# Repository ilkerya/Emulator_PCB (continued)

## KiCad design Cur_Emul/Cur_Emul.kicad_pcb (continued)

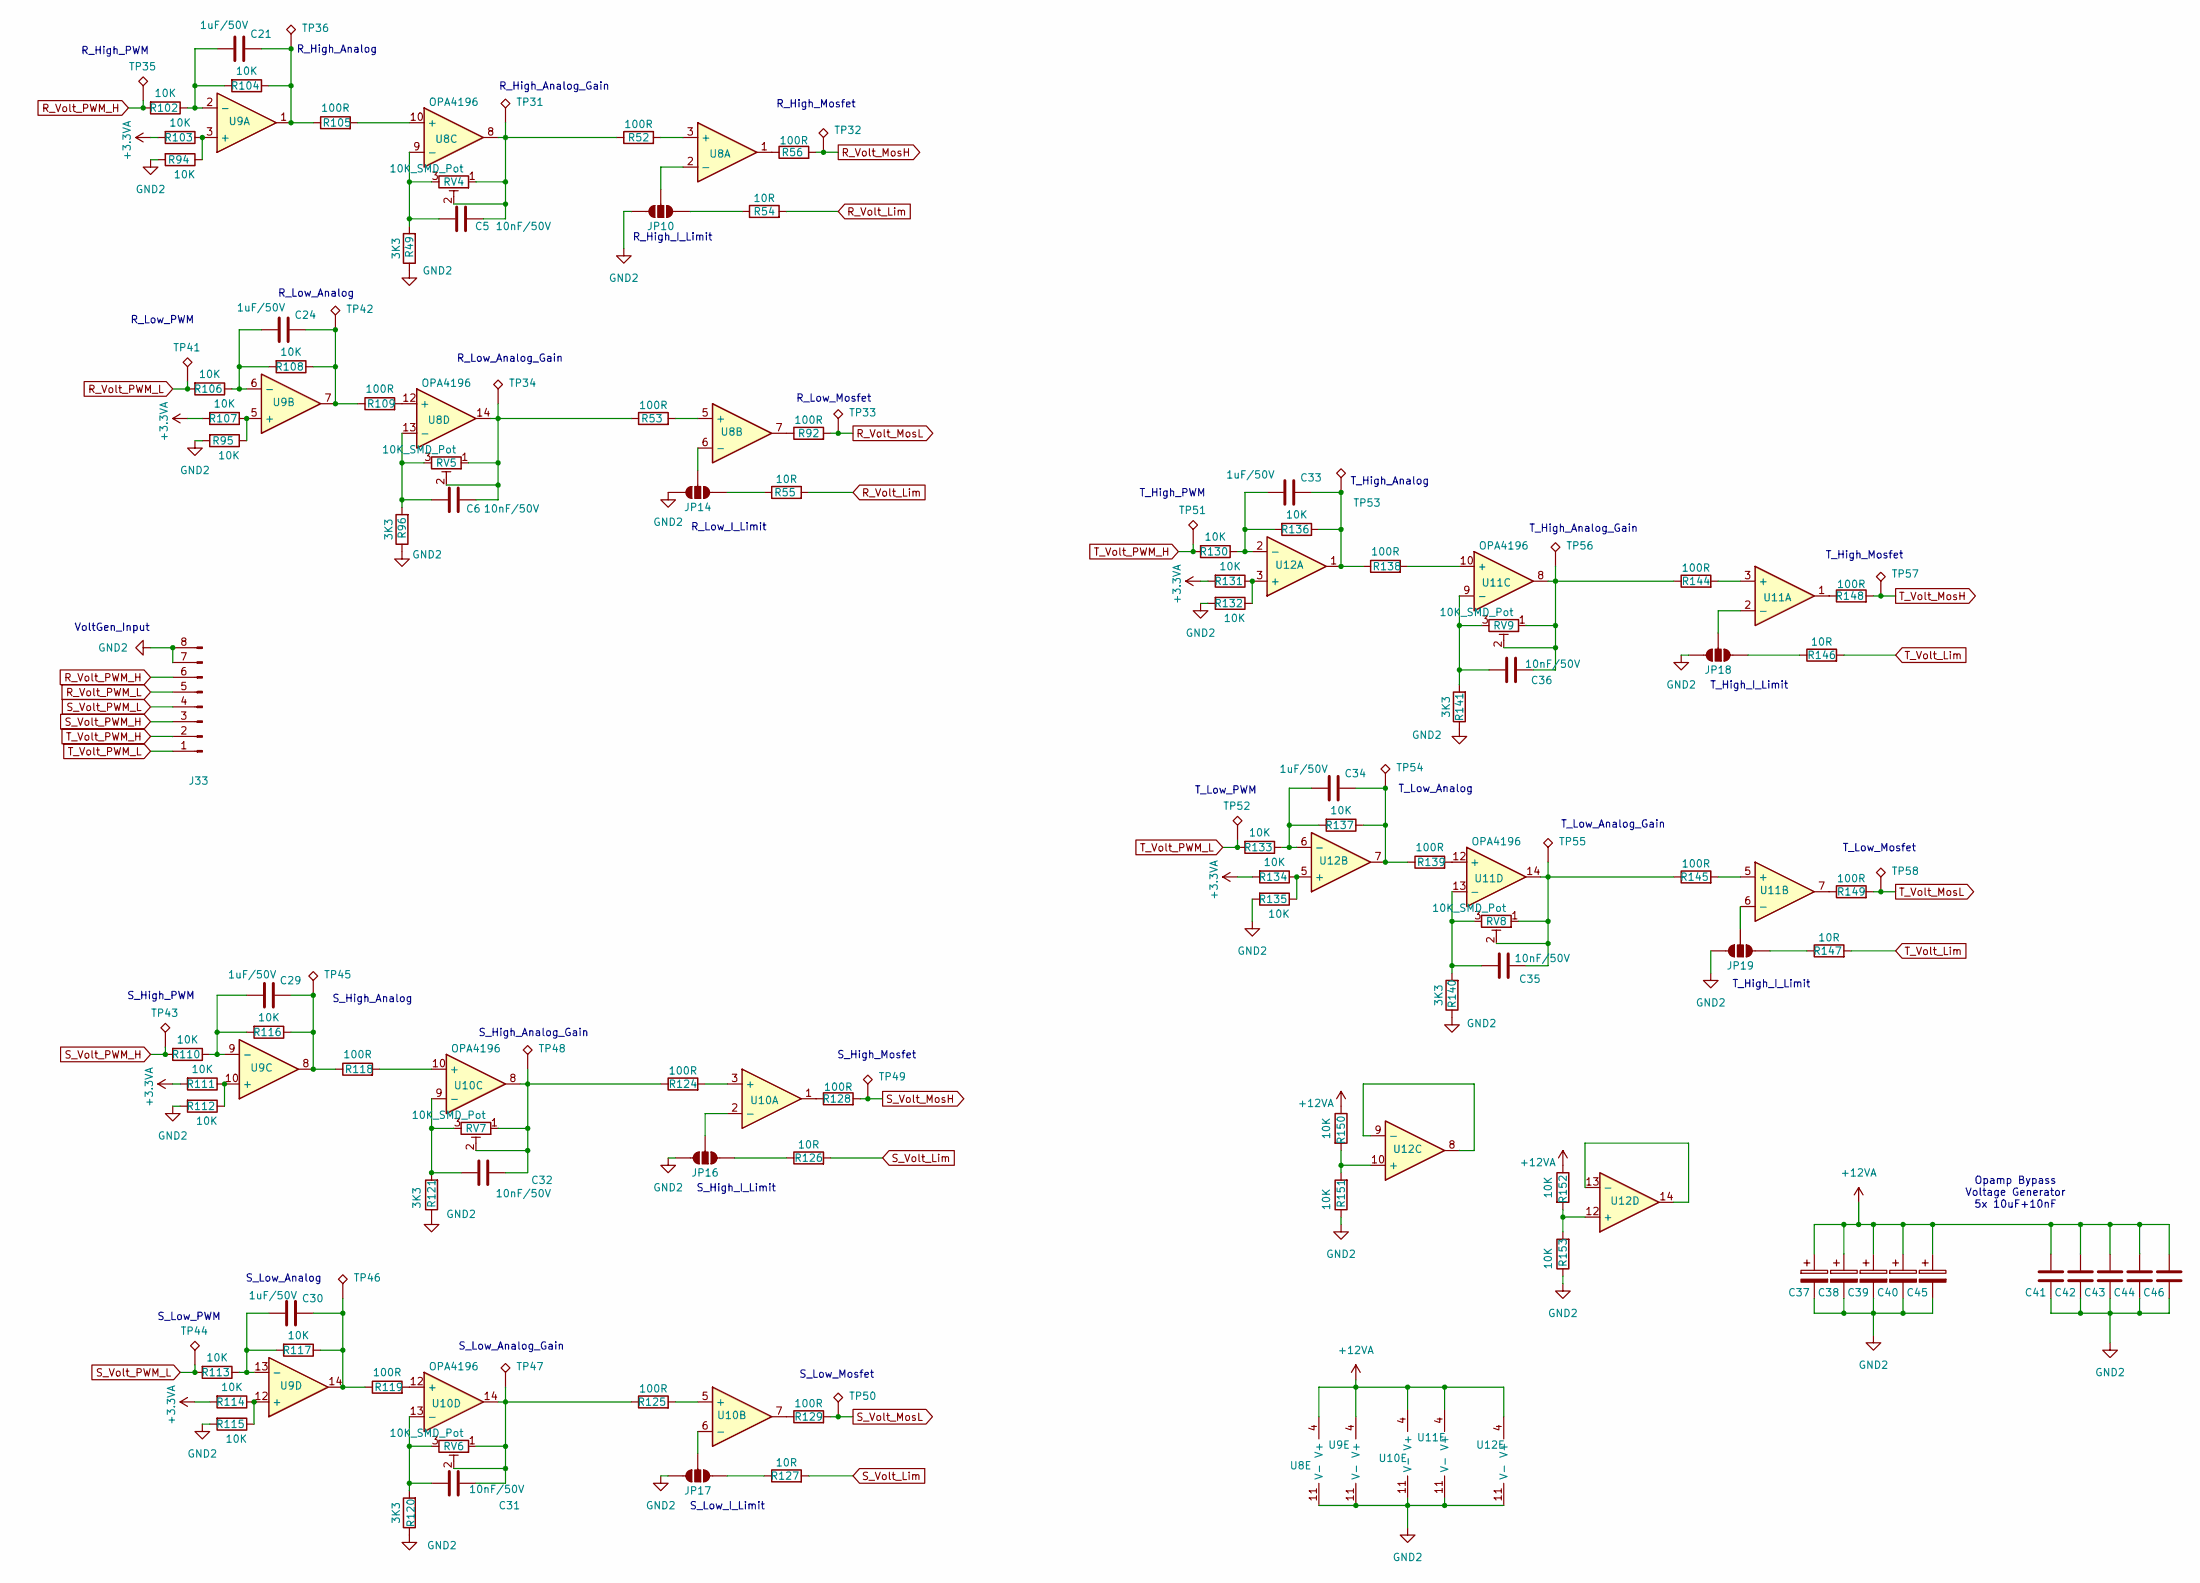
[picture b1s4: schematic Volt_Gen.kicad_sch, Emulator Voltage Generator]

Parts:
C5, C6, C31, C32, C35, C36, C41, C42, C43, C44, C46: 10nF/50V; C_0805_2012Metric_Pad1.18x1.45mm_HandSolder
C21, C24, C29, C30, C33, C34: 1uF/50V; C_1206_3216Metric_Pad1.33x1.80mm_HandSolder
C37, C38, C39, C40, C45: 10uF/50V; CP_Elec_4x3.9
J33: Conn_01x08_Pin_JST_2.0mm; JST_PH_B8B-PH-K_1x08_P2.00mm_Vertical
JP10, JP14, JP16, JP17, JP18, JP19: SolderJumper_3_Open; SolderJumper-3_P2.0mm_Open_TrianglePad1.0x1.5mm
R49, R96, R120, R121, R140, R141: 3K3; R_0805_2012Metric_Pad1.20x1.40mm_HandSolder
R52, R53, R56, R92, R105, R109, R118, R119, R124, R125, R128, R129, R138, R139, R144, R145, R148, R149: 100R; R_0805_2012Metric_Pad1.20x1.40mm_HandSolder
R54, R55, R126, R127, R146, R147: 10R; R_0805_2012Metric_Pad1.20x1.40mm_HandSolder
R94, R95, R102, R103, R104, R106, R107, R108, R110, R111, R112, R113, R114, R115, R116, R117, R130, R131, R132, R133, R134, R135, R136, R137, R150, R151, R152, R153: 10K; R_0805_2012Metric_Pad1.20x1.40mm_HandSolder
RV4, RV5, RV6, RV7, RV8, RV9: 10K_SMD_Pot; Potentiometer_Bourns_3314J_Vertical
TP31, TP32, TP33, TP34, TP35, TP36, TP41, TP42, TP43, TP44, TP45, TP46, TP47, TP48, TP49, TP50, TP51, TP52, TP53, TP54, TP55, TP56, TP57, TP58: Test_Point_THT_KeyStone; TestPoint_Loop_D1.80mm_Drill1.0mm_Beaded
U8, U9, U10, U11, U12: Opamp_Quad_OPA_4196; SOIC-14_3.9x8.7mm_P1.27mm

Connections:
+3.3VA: R103.2, R107.2, R111.2, R114.2, R131.2, R134.2; also elsewhere on the board
+12VA: C37.1, C38.1, C39.1, C40.1, C41.1, C42.1, C43.1, C44.1, C45.1, C46.1, R150.1, R152.1, U8.4 (V+), U9.4 (V+), U10.4 (V+), U11.4 (V+), U12.4 (V+); also elsewhere on the board
GND2: C37.2, C38.2, C39.2, C40.2, C41.2, C42.2, C43.2, C44.2, C45.2, C46.2, J33.7, J33.8, JP10.3 (B), JP14.3 (B), JP16.3 (B), JP17.3 (B), JP18.3 (B), JP19.3 (B), R49.1, R94.2, R95.2, R96.1, R112.2, R115.2, R120.1, R121.1, R132.2, R135.2, R140.1, R141.1, R151.1, R153.1, U8.11 (V-), U9.11 (V-), U10.11 (V-), U11.11 (V-), U12.11 (V-); also elsewhere on the board
unnamed: C5.2, R52.1, RV4.1, RV4.2, TP31.1, U8.8
unnamed: C6.2, R53.1, RV5.1, RV5.2, TP34.1, U8.14
unnamed: C21.2, R104.1, R105.1, TP36.1, U9.1
unnamed: C24.2, R108.1, R109.1, TP42.1, U9.7
unnamed: C29.2, R116.1, R118.1, TP45.1, U9.8
unnamed: C30.2, R117.1, R119.1, TP46.1, U9.14
unnamed: C31.2, R125.1, RV6.1, RV6.2, TP47.1, U10.14
unnamed: C32.2, R124.1, RV7.1, RV7.2, TP48.1, U10.8
unnamed: C33.2, R136.1, R138.1, TP53.1, U12.1
unnamed: C34.2, R137.1, R139.1, TP54.1, U12.7
unnamed: C35.2, R145.1, RV8.1, RV8.2, TP55.1, U11.14
unnamed: C36.2, R144.1, RV9.1, RV9.2, TP56.1, U11.8
unnamed: JP10.1 (A), R54.1
unnamed: JP10.2 (C), U8.2 (-)
unnamed: JP14.1 (A), R55.1
unnamed: JP14.2 (C), U8.6 (-)
unnamed: JP16.1 (A), R126.1
unnamed: JP16.2 (C), U10.2 (-)
unnamed: JP17.1 (A), R127.1
unnamed: JP17.2 (C), U10.6 (-)
unnamed: JP18.1 (A), R146.1
unnamed: JP18.2 (C), U11.2 (-)
unnamed: JP19.1 (A), R147.1
unnamed: JP19.2 (C), U11.6 (-)
unnamed: R56.1, U8.1
unnamed: R92.1, U8.7
unnamed: R128.1, U10.1
unnamed: R129.1, U10.7
unnamed: R148.1, U11.1
unnamed: R149.1, U11.7
unnamed: R52.2, U8.3 (+)
unnamed: R53.2, U8.5 (+)
unnamed: R105.2, U8.10 (+)
unnamed: C5.1, R49.2, RV4.3, U8.9 (-)
unnamed: R109.2, U8.12 (+)
unnamed: C6.1, R96.2, RV5.3, U8.13 (-)
unnamed: R94.1, R103.1, U9.3 (+)
unnamed: C21.1, R102.1, R104.2, U9.2 (-)
unnamed: R95.1, R107.1, U9.5 (+)
unnamed: C24.1, R106.1, R108.2, U9.6 (-)
unnamed: R111.1, R112.1, U9.10 (+)
unnamed: C29.1, R110.1, R116.2, U9.9 (-)
unnamed: R114.1, R115.1, U9.12 (+)
unnamed: C30.1, R113.1, R117.2, U9.13 (-)
unnamed: R124.2, U10.3 (+)
unnamed: R125.2, U10.5 (+)
unnamed: R118.2, U10.10 (+)
unnamed: C32.1, R121.2, RV7.3, U10.9 (-)
unnamed: R119.2, U10.12 (+)
unnamed: C31.1, R120.2, RV6.3, U10.13 (-)
unnamed: R144.2, U11.3 (+)
unnamed: R145.2, U11.5 (+)
unnamed: R138.2, U11.10 (+)
unnamed: C36.1, R141.2, RV9.3, U11.9 (-)
unnamed: R139.2, U11.12 (+)
unnamed: C35.1, R140.2, RV8.3, U11.13 (-)
unnamed: R131.1, R132.1, U12.3 (+)
unnamed: C33.1, R130.1, R136.2, U12.2 (-)
unnamed: R134.1, R135.1, U12.5 (+)
unnamed: C34.1, R133.1, R137.2, U12.6 (-)
unnamed: R150.2, R151.2, U12.10 (+)
unnamed: U12.8, U12.9 (-)
unnamed: R152.2, R153.2, U12.12 (+)
unnamed: U12.13 (-), U12.14
R_Volt_Lim: R54.2, R55.2; also elsewhere on the board
R_Volt_MosH: R56.2, TP32.1; also elsewhere on the board
R_Volt_MosL: R92.2, TP33.1; also elsewhere on the board
R_Volt_PWM_H: J33.6, R102.2, TP35.1
R_Volt_PWM_L: J33.5, R106.2, TP41.1
S_Volt_Lim: R126.2, R127.2; also elsewhere on the board
S_Volt_MosH: R128.2, TP49.1; also elsewhere on the board
S_Volt_MosL: R129.2, TP50.1; also elsewhere on the board
S_Volt_PWM_H: J33.3, R110.2, TP43.1
S_Volt_PWM_L: J33.4, R113.2, TP44.1
T_Volt_Lim: R146.2, R147.2; also elsewhere on the board
T_Volt_MosH: R148.2, TP57.1; also elsewhere on the board
T_Volt_MosL: R149.2, TP58.1; also elsewhere on the board
T_Volt_PWM_H: J33.2, R130.2, TP51.1
T_Volt_PWM_L: J33.1, R133.2, TP52.1

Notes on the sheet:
S_Low_Analog_Gain
S_High_I_Limit
R_Low_PWM
S_High_Analog_Gain
S_Low_PWM
T_Low_Analog
R_Low_Analog
R_Low_I_Limit
R_Low_Analog_Gain
T_Low_PWM
T_Low_Analog_Gain
S_High_Mosfet
S_Low_Analog
S_Low_I_Limit
S_Low_Mosfet
R_High_I_Limit
R_High_Analog
T_High_Mosfet
R_High_PWM
S_High_PWM
T_Low_Mosfet
T_High_I_Limit
T_High_Analog
T_High_PWM
Opamp Bypass Voltage Generator 5x 10uF+10nF
T_High_Analog_Gain
R_Low_Mosfet
S_High_Analog
VoltGen_Input
R_High_Mosfet
R_High_Analog_Gain

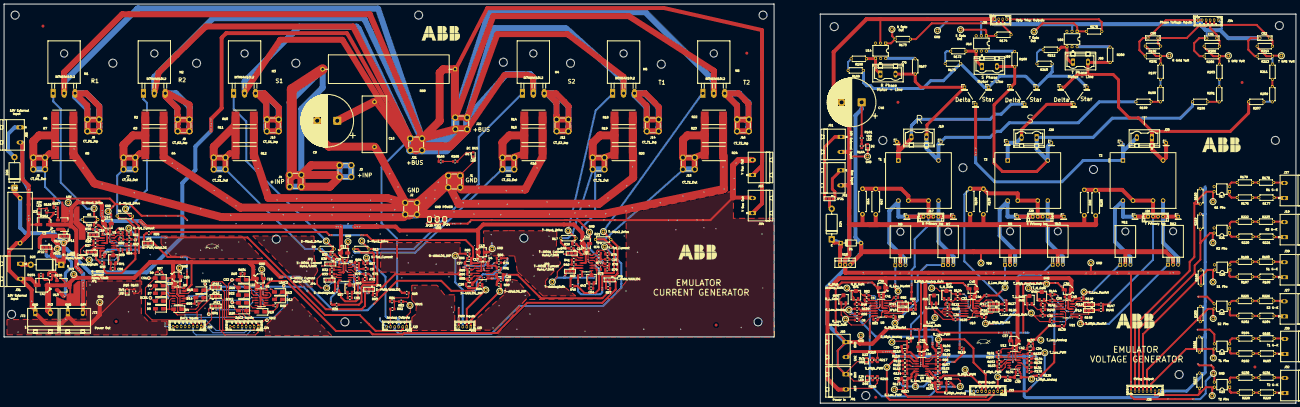
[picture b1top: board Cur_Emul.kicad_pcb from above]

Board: 2 copper layers, 644.3 x 199.1 mm, 525 parts (0 on the bottom side), 289 nets.

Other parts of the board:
C9: 300uF/50V; CP_Radial_D26.0mm_P10.00mm_SnapIn
C10: 1uF/50V MKT; C_Rect_L28.0mm_W12.0mm_P22.50mm_MKS4
Fiducial: Fiducial_1.5mm_Mask3mm
Fiducial#2, Fiducial#3, Fiducial#4, Fiducial#5, Fiducial#6, Fiducial#7, Fiducial#8: Fiducial_1.5mm_Mask3mm
J1, J2, J3, J4, J5, J6, J7, J8, J9, J10, J11, J12, J13, J14, J15, J16, J21, J22: Wuerth_REDCUBE-74651175_ScrewTerminal; Wuerth_REDCUBE-THR_WP-THRSH_74651175_THR
JP20, JP23, JP24: SolderJumper_2_Bridged; SolderJumper-2_P1.3mm_Bridged2Bar_RoundedPad1.0x1.5mm
M1, M2, M3, M4, M5, M6: IXTH64N10L2; TO-247-3_Horizontal_TabDown
M7, M8, M9, M10, M11, M12: IRF530; TO-220-3_Horizontal_TabDown
R2, R3, R4, R6, R7, R8, R10, R11, R12, R14, R15, R16, R18, R19, R20, R22, R23, R24: 10mOhm_Vishay_WSR3_Shunt; R_Shunt_Vishay_WSR2_WSR3
R44, R47, R48, R158, R159, R160: 4R7/2W; R_Axial_DIN0411_L9.9mm_D3.6mm_P12.70mm_Horizontal
R68: 1R/100W; R_Axial_Power_L60.0mm_W14.0mm_P66.04mm
T1, T2, T3: Transformer_1P_2S; Transformer_Myrra_EI30-5_44000_Horizontal

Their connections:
GND: JP20.2 (B), JP23.2 (B), JP24.2 (B); also elsewhere on the board
GND2: R44.2, R47.2, R48.2, R158.2, R159.2, R160.2; also elsewhere on the board
GNDPWR: C9.2, C10.2, J1.1, J2.1, JP20.1 (A), JP23.1 (A), JP24.1 (A), R2.2, R3.2, R4.2, R6.2, R7.2, R8.2, R10.2, R11.2, R12.2, R14.2, R15.2, R16.2, R18.2, R19.2, R20.2, R22.2, R23.2, R24.2; also elsewhere on the board
unnamed: J3.1, J4.1, R68.1
unnamed: J6.1, M1.3 (S)
unnamed: J8.1, M2.3 (S)
unnamed: J10.1, M3.3 (S)
unnamed: J12.1, M4.3 (S)
unnamed: J14.1, M5.3 (S)
unnamed: J16.1, M6.3 (S)
R_MosD_1: M1.1 (G); also elsewhere on the board
R_MosD_2: M2.1 (G); also elsewhere on the board
R_Mos_I_1: J5.1, R6.1, R7.1, R8.1; also elsewhere on the board
R_Mos_I_2: J7.1, R2.1, R3.1, R4.1; also elsewhere on the board
R_Prim_H: M7.3 (S), T1.6 (SA); also elsewhere on the board
R_Prim_L: M8.3 (S), T1.10 (SD); also elsewhere on the board
R_Sec_a: T1.1 (AA); also elsewhere on the board
R_Sec_b: T1.5 (AB); also elsewhere on the board
R_Volt_Lim: R44.1, R47.1, T1.7 (SB), T1.9 (SC); also elsewhere on the board
R_Volt_MosH: M7.1 (G); also elsewhere on the board
R_Volt_MosL: M8.1 (G); also elsewhere on the board
S_MosD_1: M3.1 (G); also elsewhere on the board
S_MosD_2: M4.1 (G); also elsewhere on the board
S_Mos_I_1: J9.1, R10.1, R11.1, R12.1; also elsewhere on the board
S_Mos_I_2: J11.1, R14.1, R15.1, R16.1; also elsewhere on the board
S_Prim_H: M10.3 (S), T3.6 (SA); also elsewhere on the board
S_Prim_L: M9.3 (S), T3.10 (SD); also elsewhere on the board
S_Sec_a: T3.1 (AA); also elsewhere on the board
S_Sec_b: T3.5 (AB); also elsewhere on the board
S_Volt_Lim: R158.1, R159.1, T3.7 (SB), T3.9 (SC); also elsewhere on the board
S_Volt_MosH: M10.1 (G); also elsewhere on the board
S_Volt_MosL: M9.1 (G); also elsewhere on the board
T_MosD_1: M5.1 (G); also elsewhere on the board
T_MosD_2: M6.1 (G); also elsewhere on the board
T_Mos_I_1: J13.1, R18.1, R19.1, R20.1; also elsewhere on the board
T_Mos_I_2: J15.1, R22.1, R23.1, R24.1; also elsewhere on the board
T_Prim_H: M12.3 (S), T2.6 (SA); also elsewhere on the board
T_Prim_L: M11.3 (S), T2.10 (SD); also elsewhere on the board
T_Sec_a: T2.1 (AA); also elsewhere on the board
T_Sec_b: T2.5 (AB); also elsewhere on the board
T_Volt_Lim: R48.1, R160.1, T2.7 (SB), T2.9 (SC); also elsewhere on the board
T_Volt_MosH: M12.1 (G); also elsewhere on the board
T_Volt_MosL: M11.1 (G); also elsewhere on the board
VBUS: C9.1, C10.1, J21.1, J22.1, M1.2 (D), M2.2 (D), M3.2 (D), M4.2 (D), M5.2 (D), M6.2 (D), R68.2; also elsewhere on the board
VDD: M7.2 (D), M8.2 (D), M9.2 (D), M10.2 (D), M11.2 (D), M12.2 (D); also elsewhere on the board

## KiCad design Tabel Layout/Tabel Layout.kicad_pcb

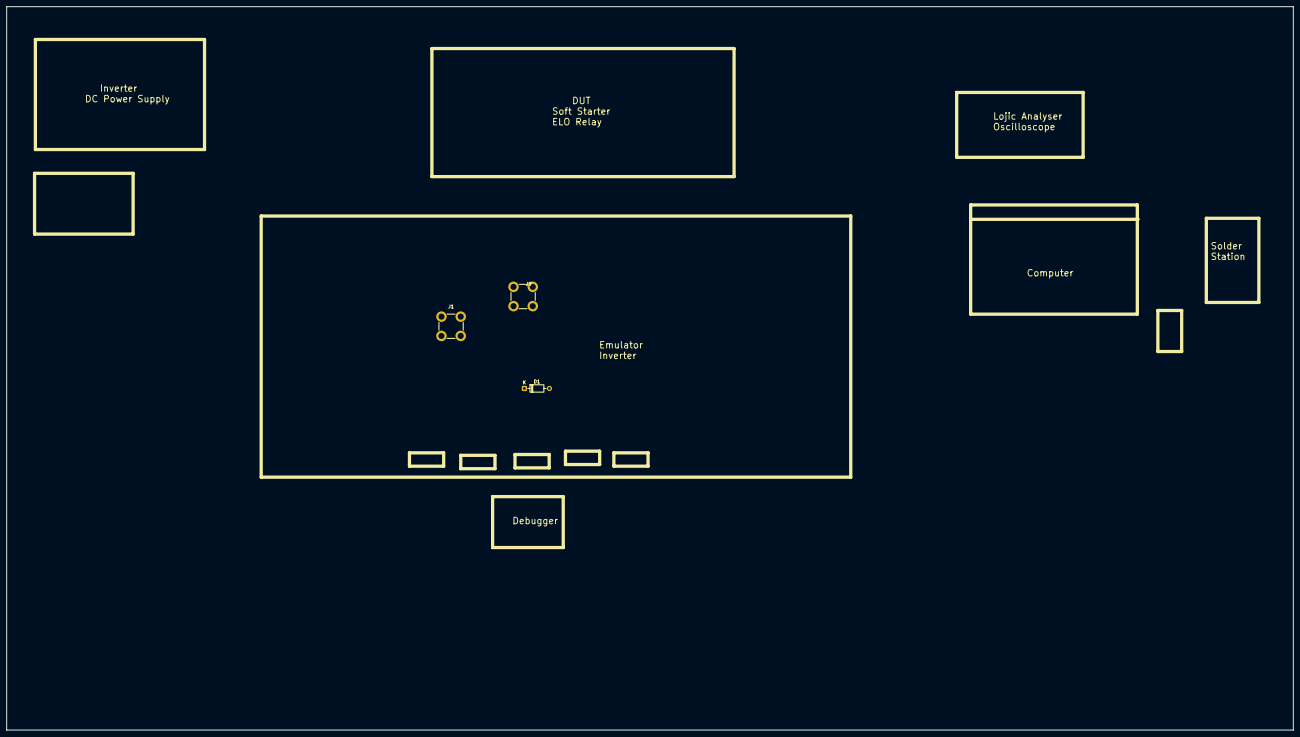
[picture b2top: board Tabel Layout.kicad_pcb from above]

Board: 2 copper layers, 391.8 x 220.2 mm, 3 parts (0 on the bottom side), 2 nets, no tracks yet.

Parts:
D1: 1N914; D_DO-35_SOD27_P7.62mm_Horizontal
J1, J9: Screw_Terminal_01x01; Wuerth_REDCUBE-THR_WP-THRSH_74651175_THR

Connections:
GND: D1.2 (A), J9.1
try: D1.1 (K), J1.1

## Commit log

2025-09-16 first
2025-09-25 pdf updates
2025-09-25 pdf updates2
2025-09-28 updates2
2025-09-29 updates3
2025-09-29 updates4
2025-10-06 with Fabr. Outputs
2025-10-10 Sch issue Fix
